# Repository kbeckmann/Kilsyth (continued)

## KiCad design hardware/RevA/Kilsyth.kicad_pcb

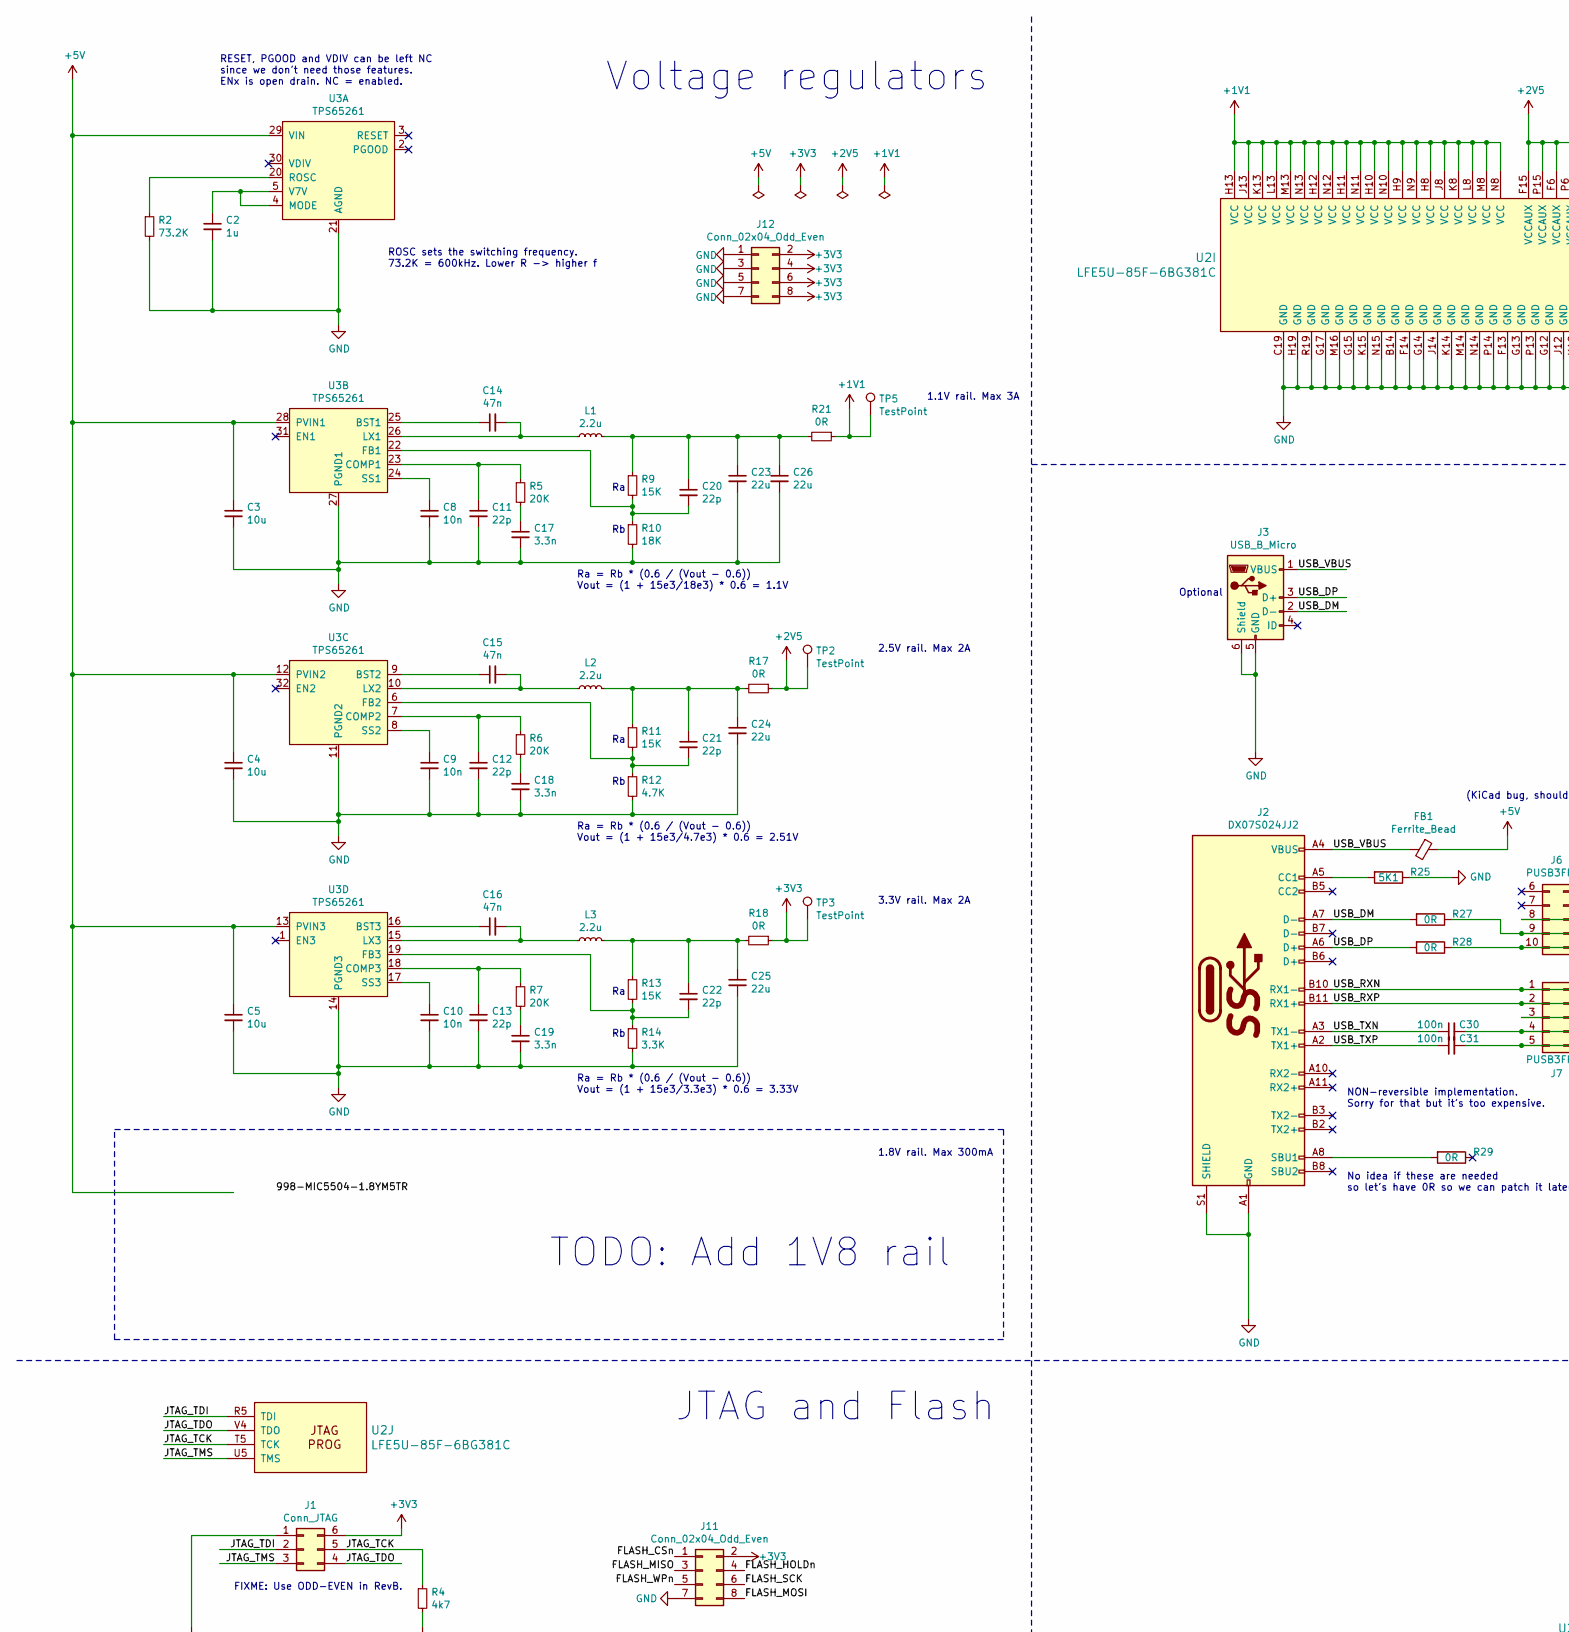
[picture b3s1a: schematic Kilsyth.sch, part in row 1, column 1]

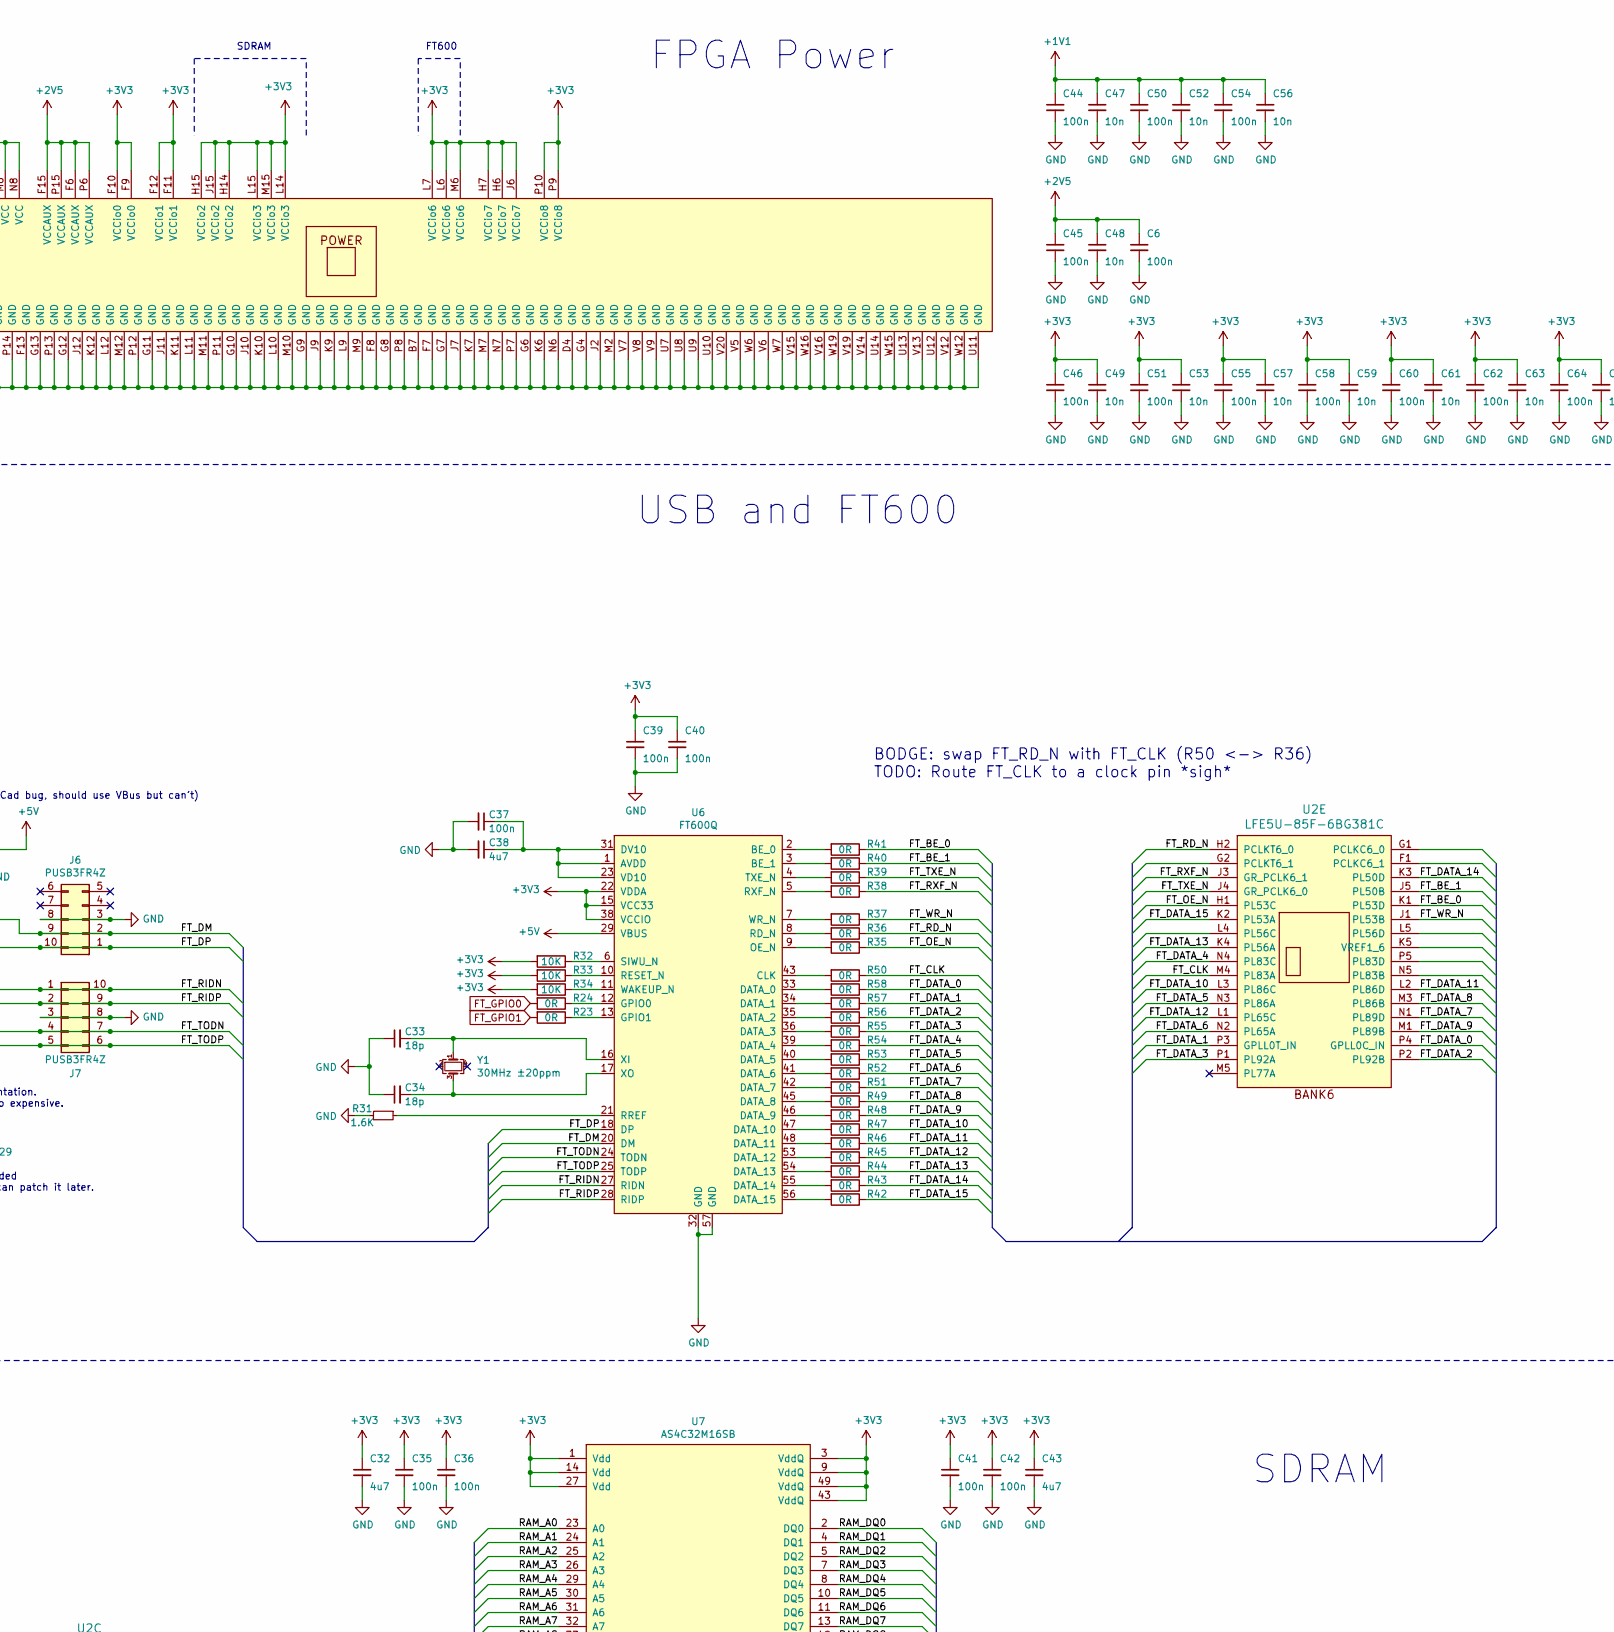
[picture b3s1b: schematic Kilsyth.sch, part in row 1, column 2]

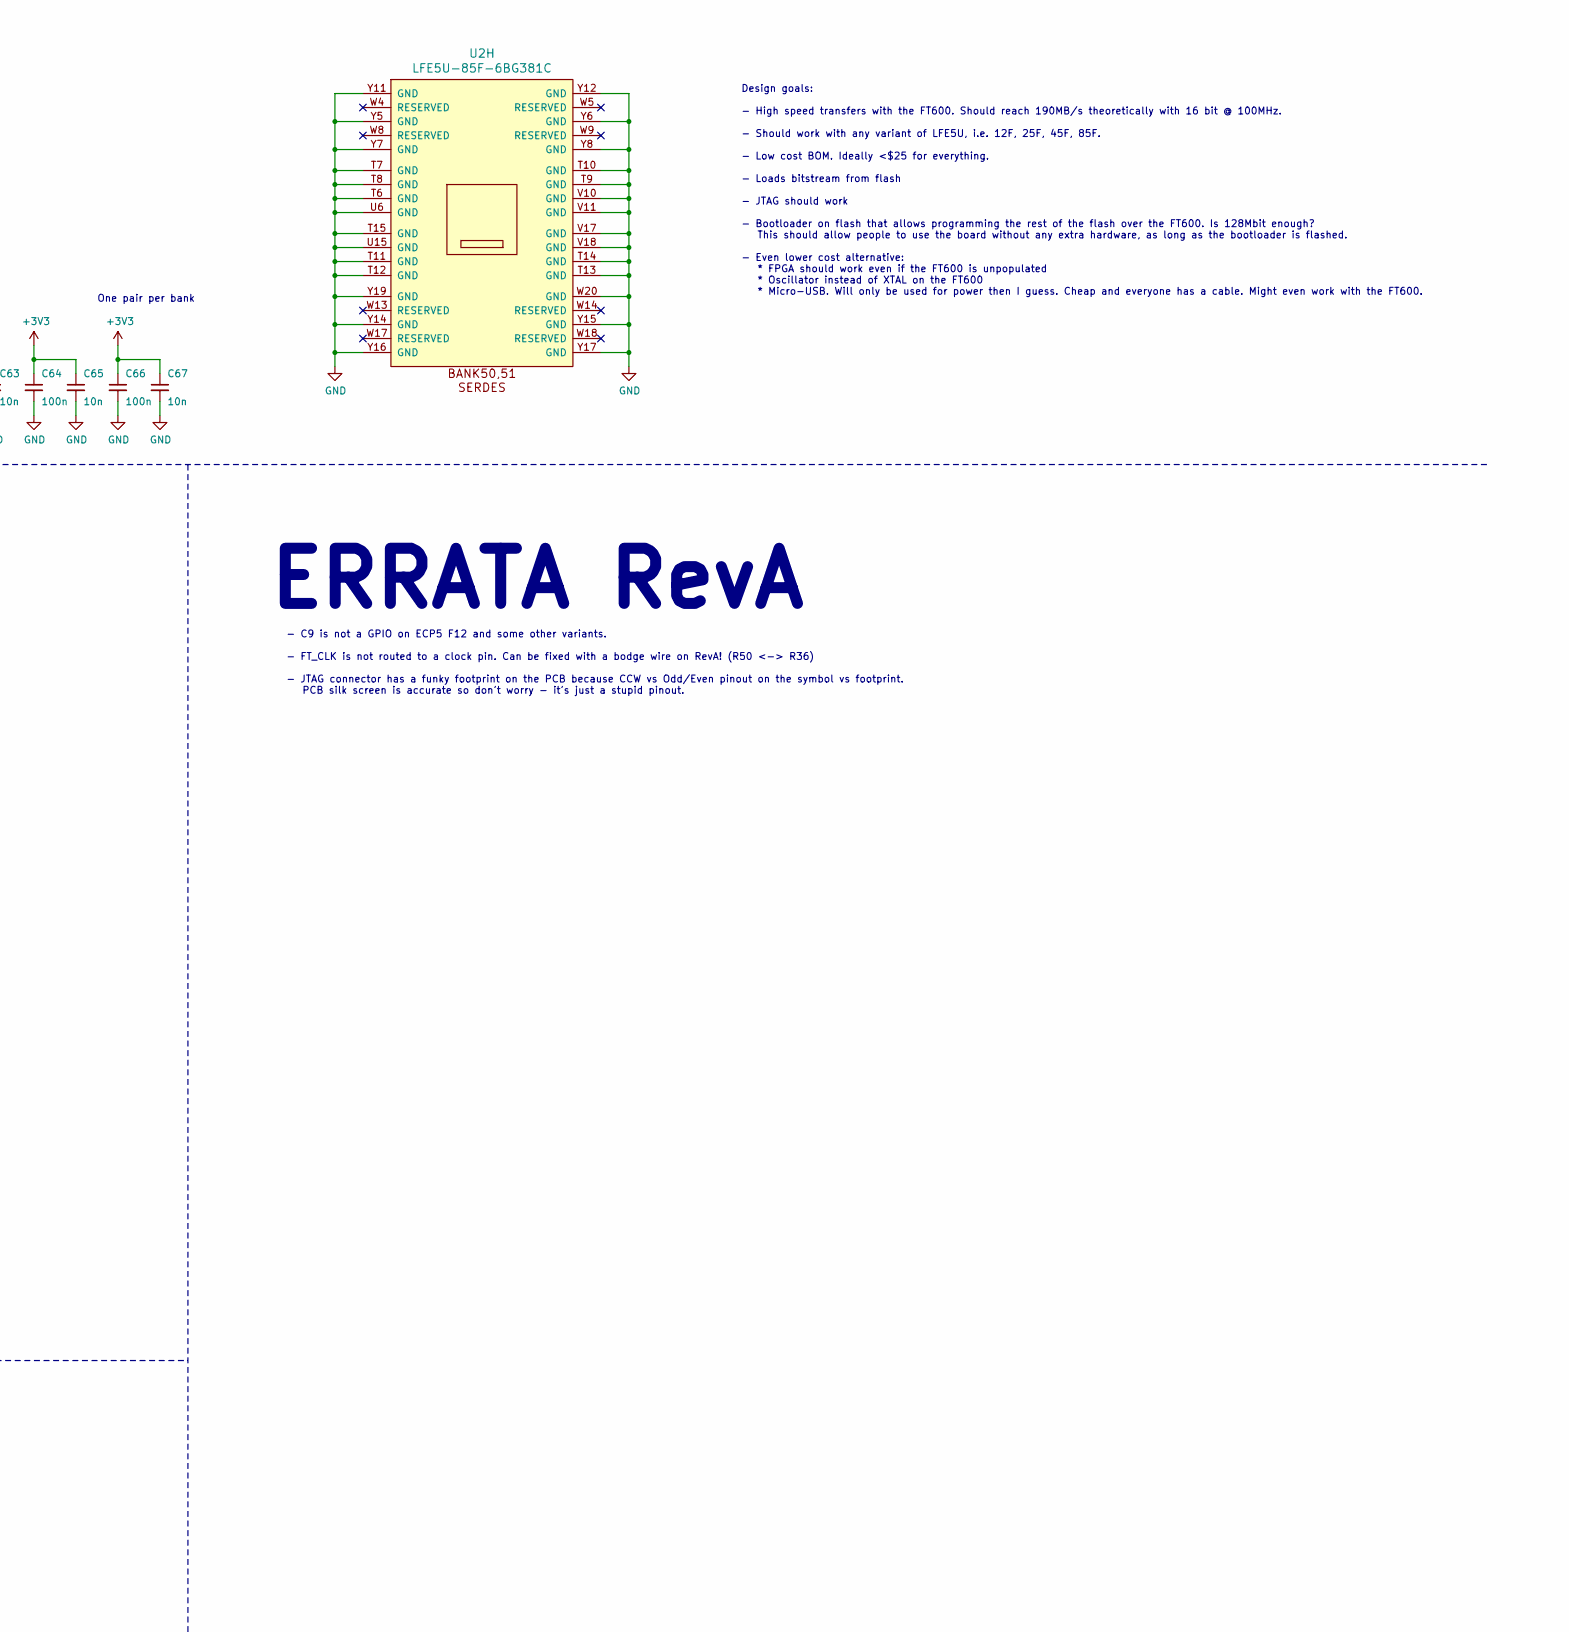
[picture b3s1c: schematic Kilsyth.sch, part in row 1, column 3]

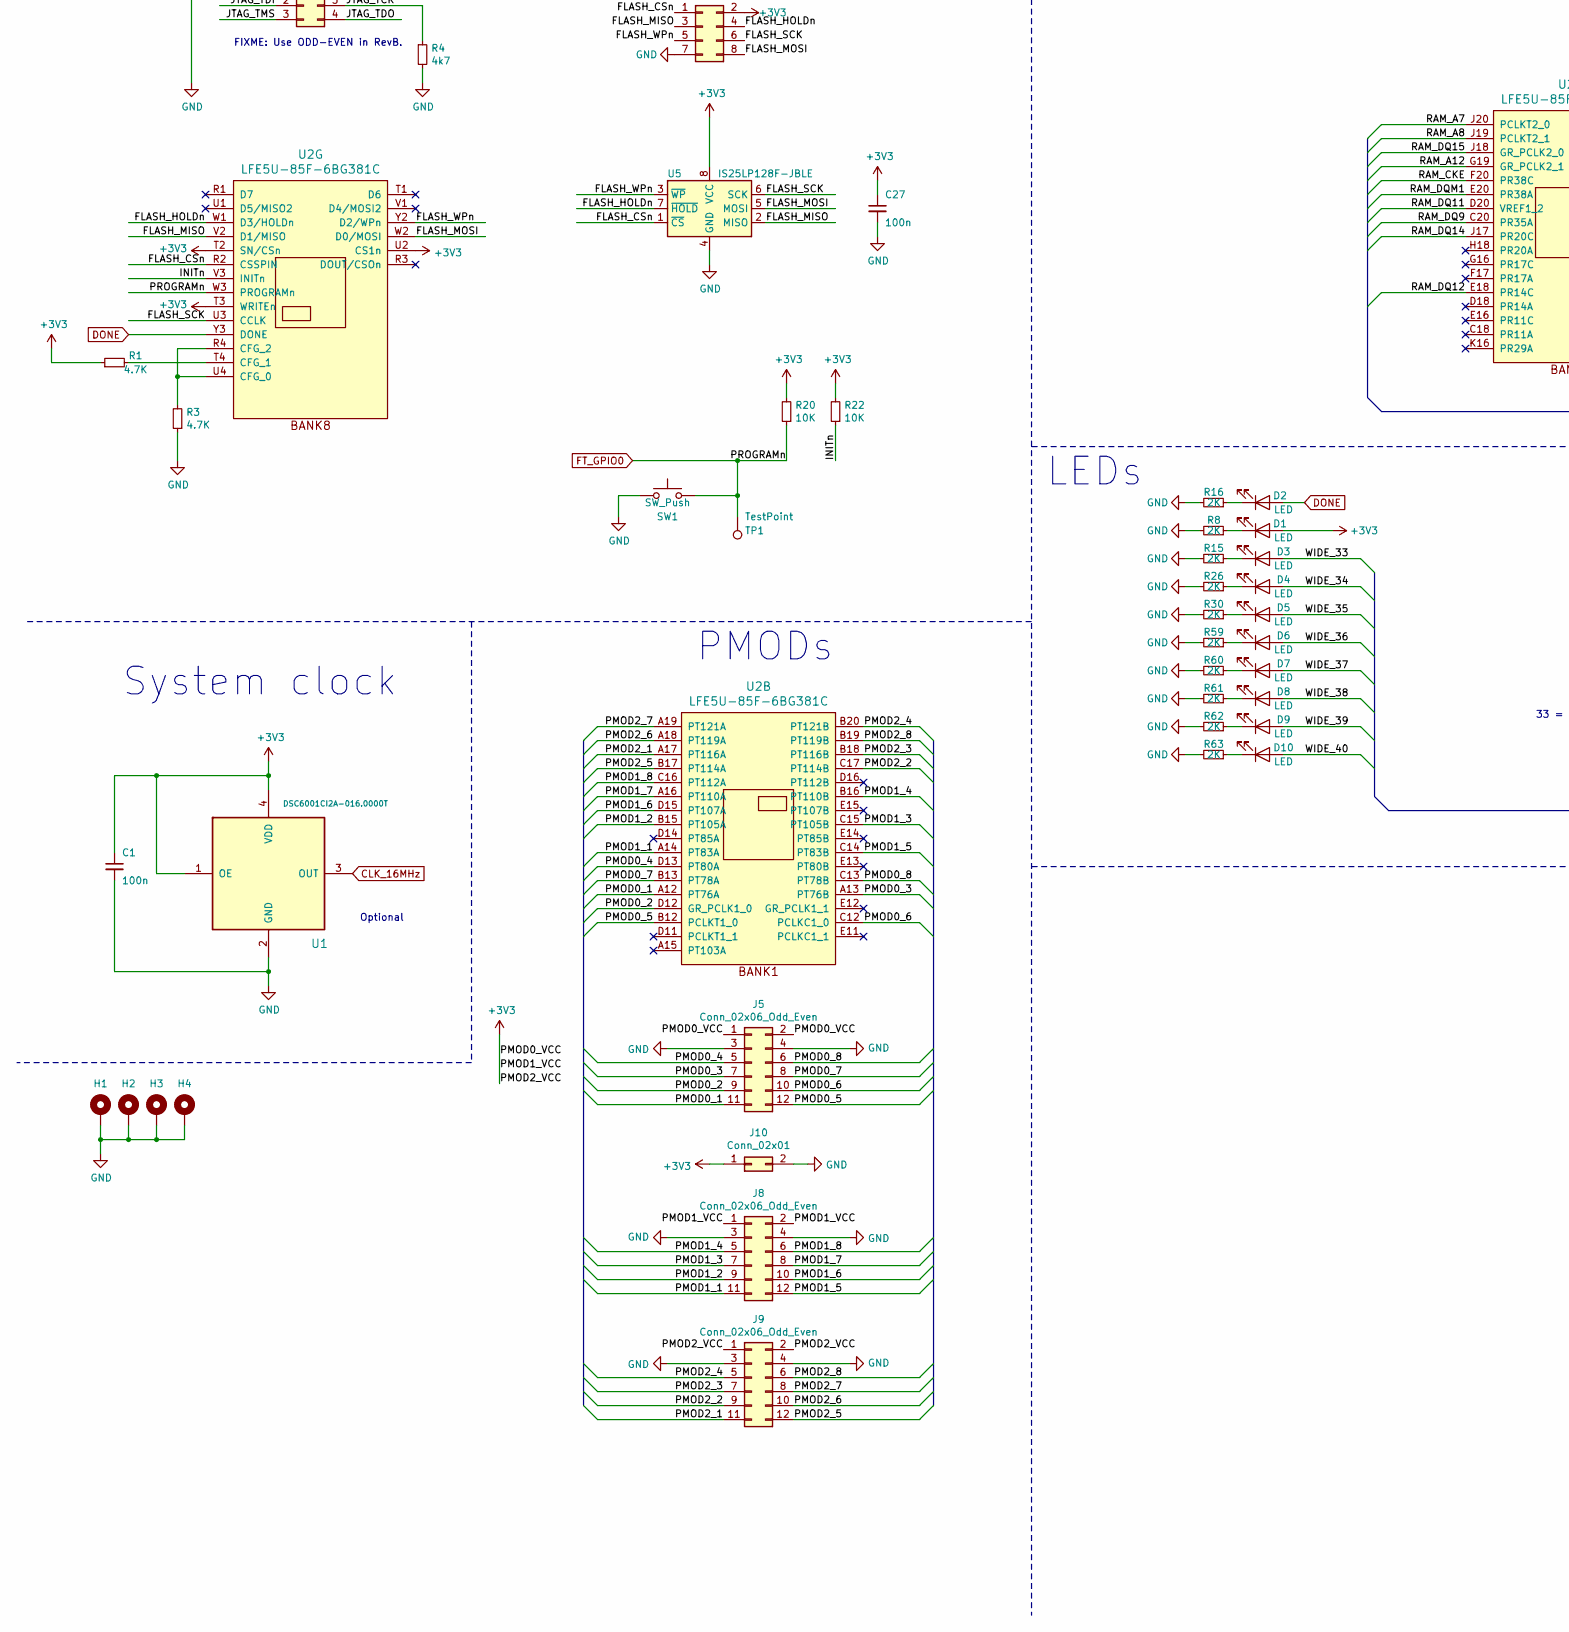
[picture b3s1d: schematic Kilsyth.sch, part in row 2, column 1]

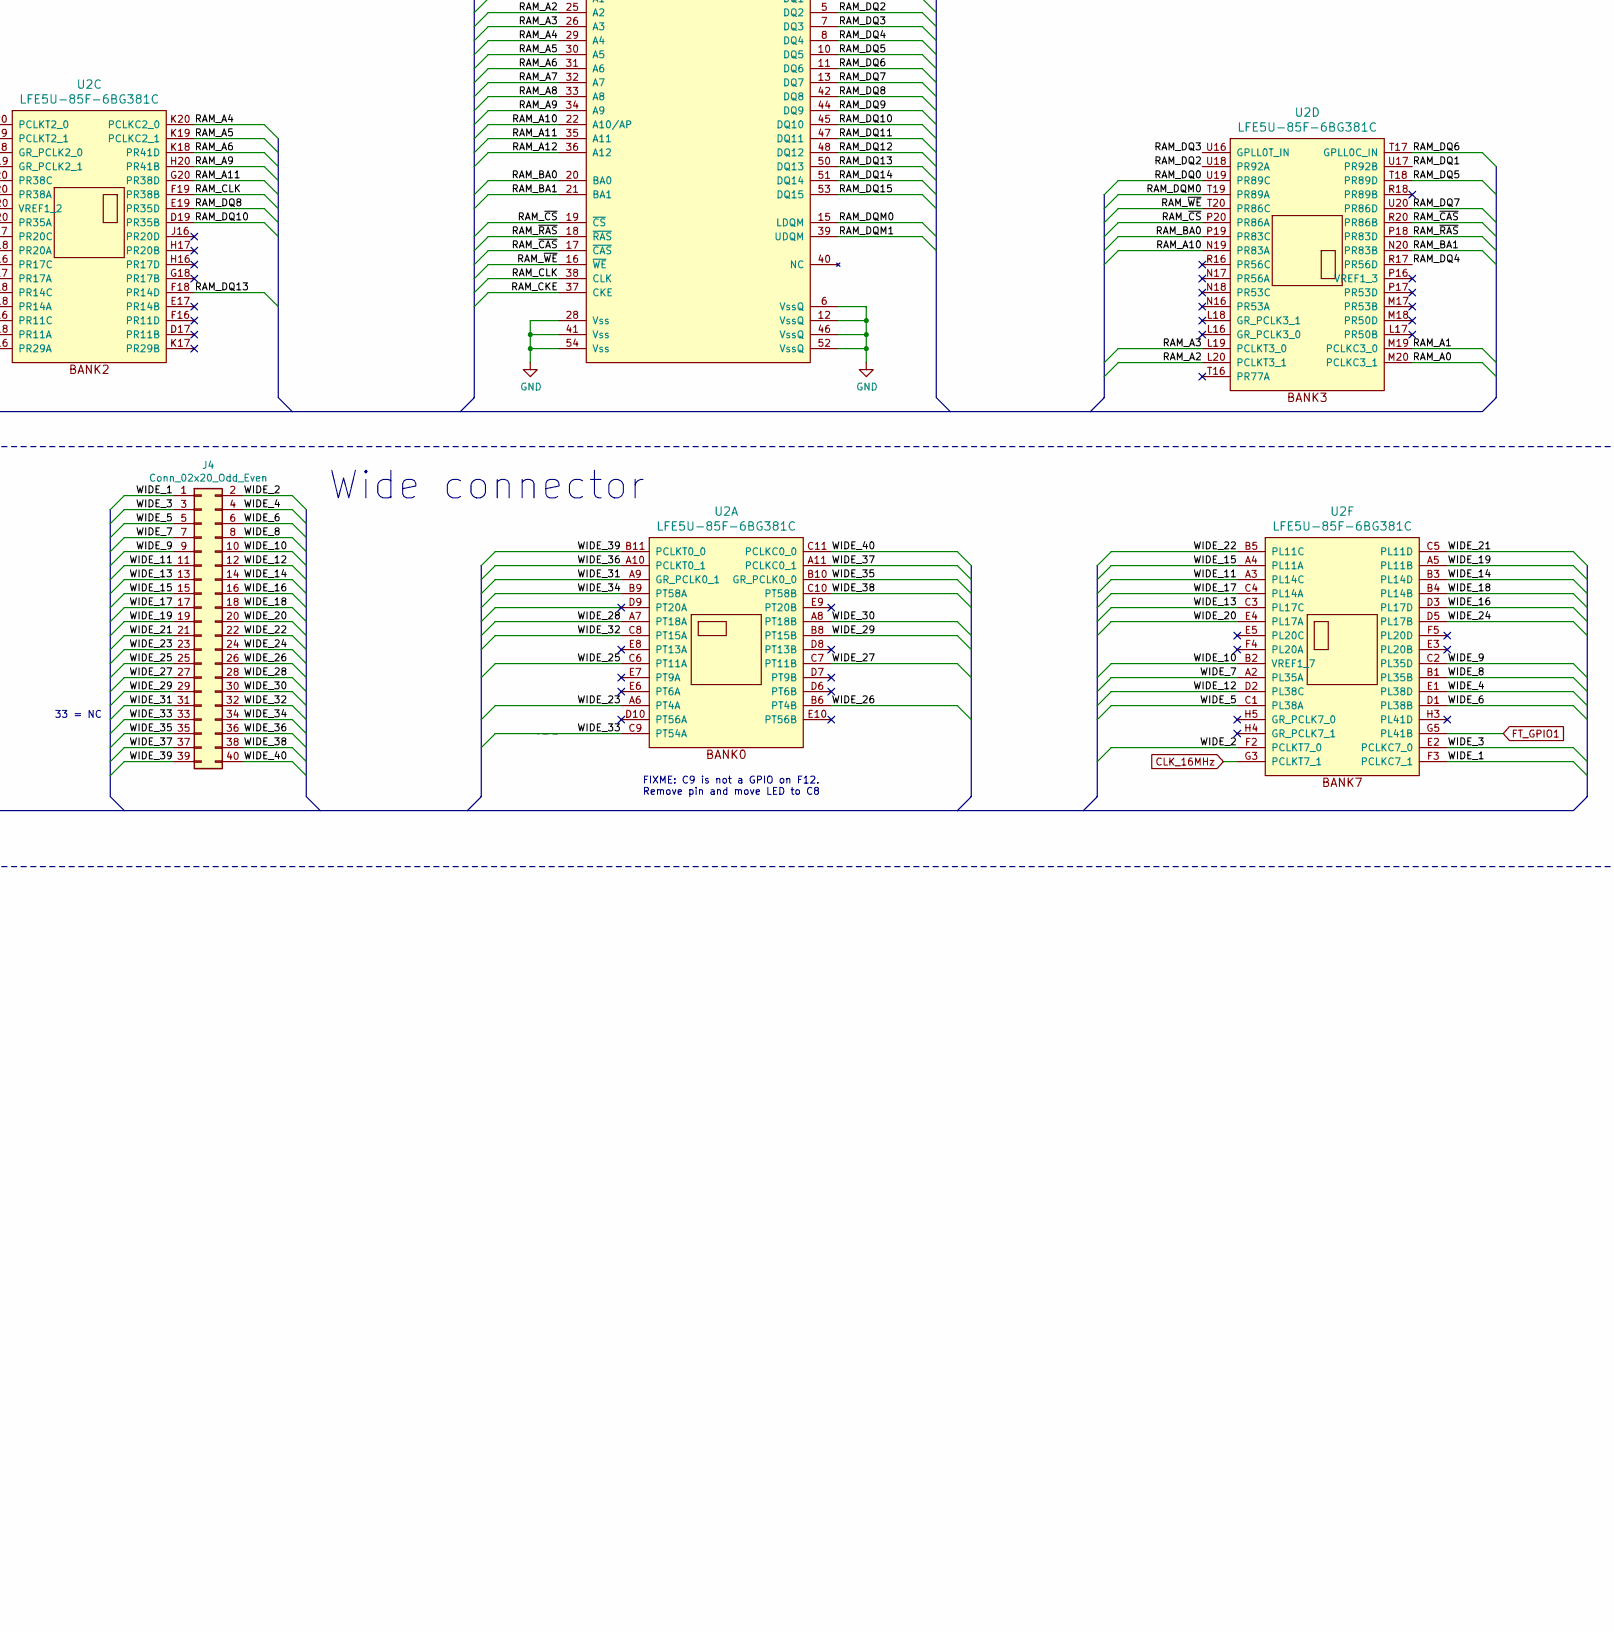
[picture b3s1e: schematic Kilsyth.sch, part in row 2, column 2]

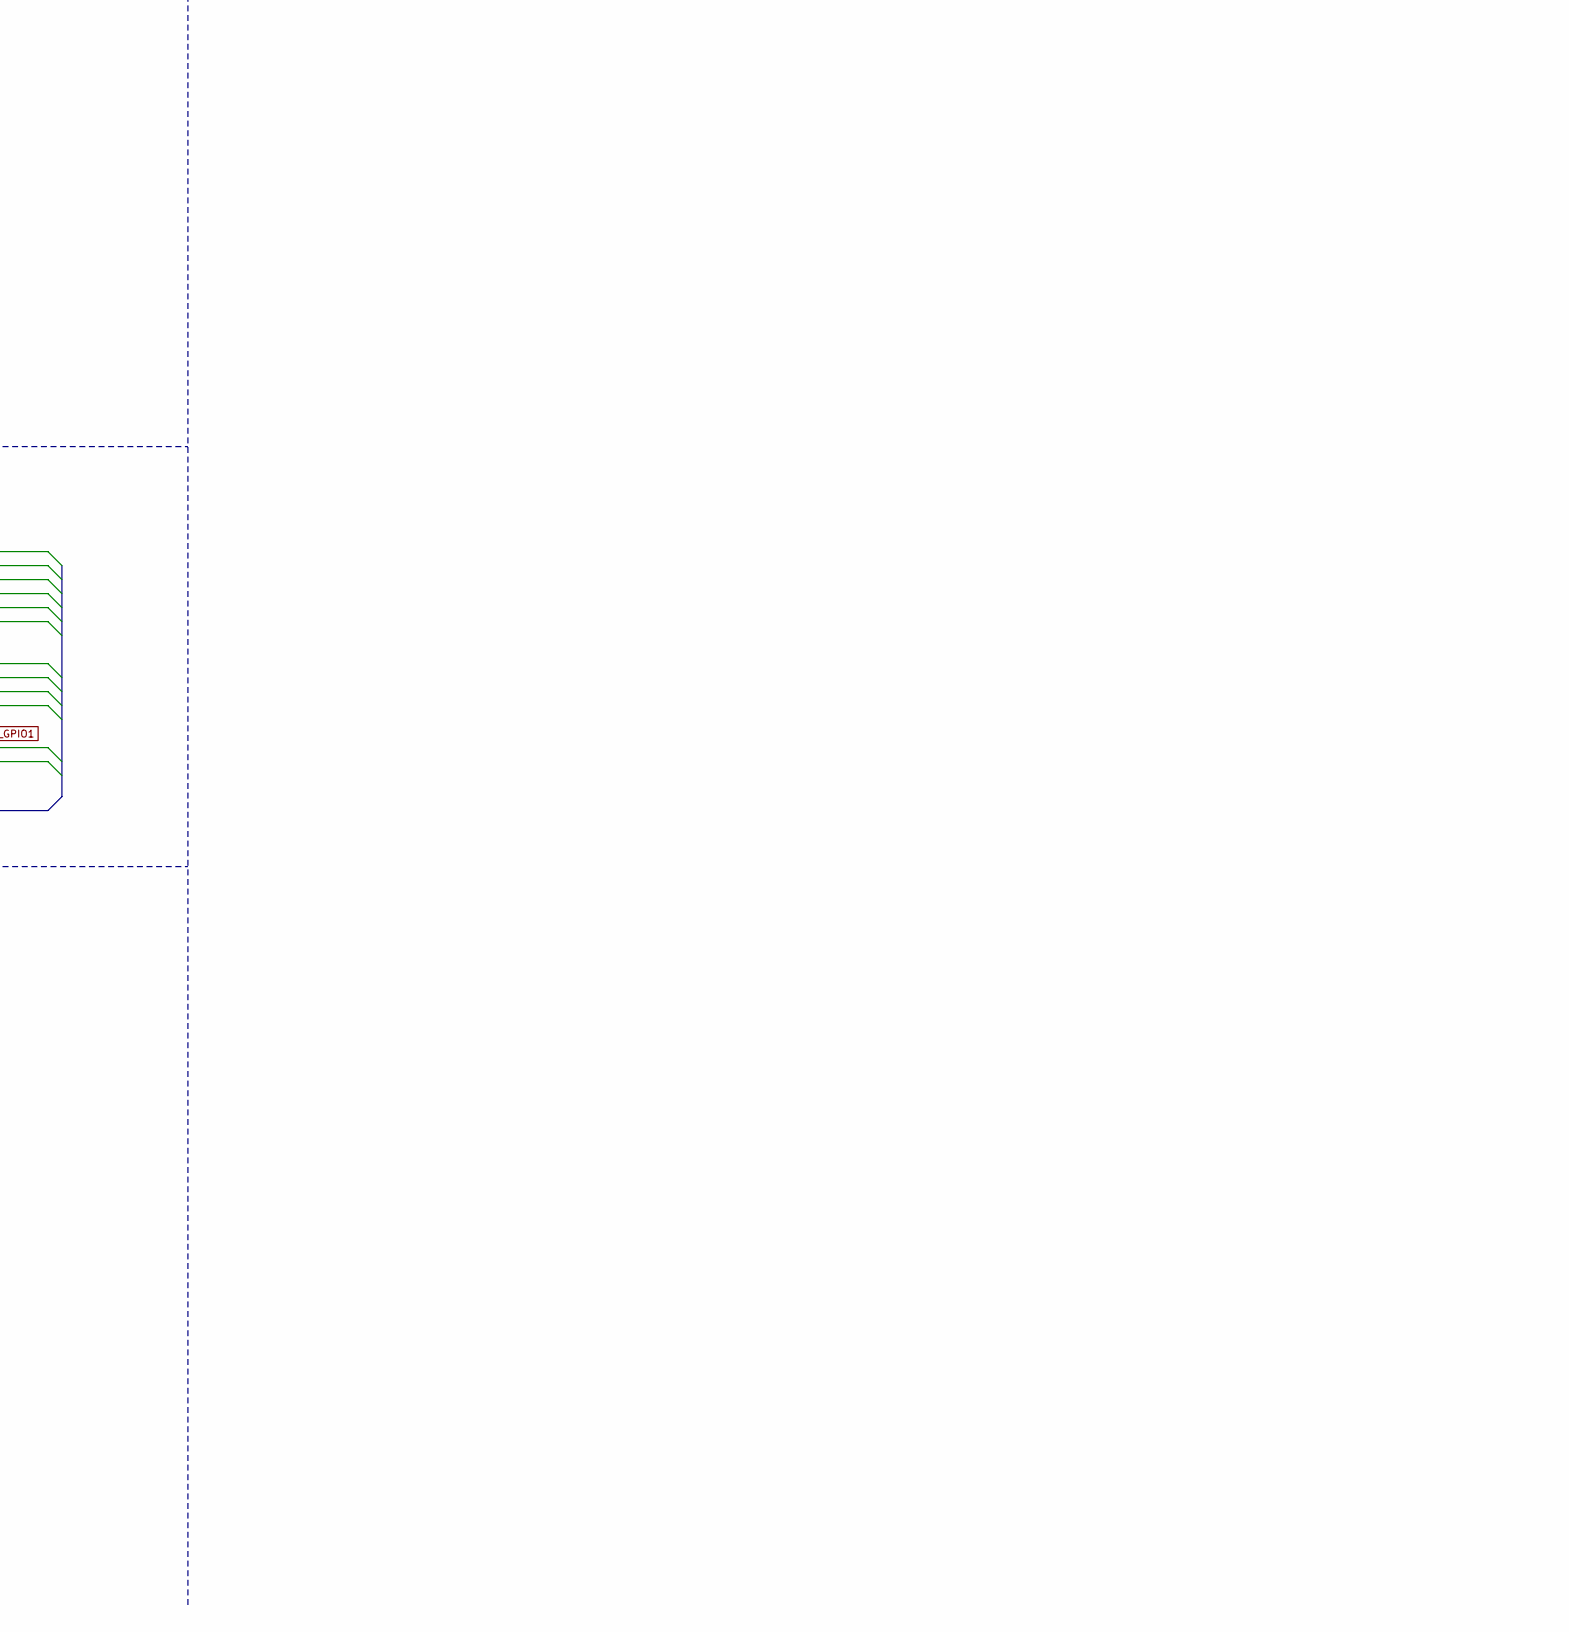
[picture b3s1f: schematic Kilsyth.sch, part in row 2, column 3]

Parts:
C1, C6, C27, C30, C31, C35, C36, C37, C39, C40, C41, C42, C44, C45, C46, C50, C51, C54, C55, C58, C60, C62, C64, C66: 100n; C_0603_1608Metric
C2: 1u; C_0603_1608Metric
C3, C4, C5: 10u; C_0603_1608Metric
C8, C9, C10, C47, C48, C49, C52, C53, C56, C57, C59, C61, C63, C65, C67: 10n; C_0603_1608Metric
C11, C12, C13, C20, C21, C22: 22p; C_0603_1608Metric
C14, C15, C16: 47n; C_0603_1608Metric
C17, C18, C19: 3.3n; C_0603_1608Metric
C23, C24, C25, C26: 22u; C_0603_1608Metric
C32, C38, C43: 4u7; C_0603_1608Metric
C33, C34: 18p; C_0603_1608Metric
D1, D2, D3, D4, D5, D6, D7, D8, D9, D10: LED; LED_0603_1608Metric
FB1: Ferrite_Bead; L_0603_1608Metric
H1, H2, H3, H4: MountingHole_3.2mm_M3_Pad
J1: Conn_JTAG; PinHeader_2x03_P2.54mm_Vertical_SMD
J2: DX07S024JJ2; USBC_DX07S024JJ2R1300; Mouser 656-DX07S024JJ2R1300
J3: USB_B_Micro; USB_Micro-B_Molex-105017-0001
J4: Conn_02x20_Odd_Even; PinHeader_2x20_P2.54mm_Vertical_SMD
J5, J8, J9: Conn_02x06_Odd_Even; PinSocket_2x06_P2.54mm_Horizontal
J6, J7: PUSB3FR4Z; Mouser 771-PUSB3FR4Z
J10: Conn_02x01; PinHeader_2x01_P2.54mm_Vertical
J11, J12: Conn_02x04_Odd_Even; PinHeader_2x04_P2.54mm_Vertical_SMD
L1, L2, L3: 2.2u; L_1008_1210; Mouser 81-DFE322512F-2R2MP2
R1, R3, R12: 4.7K; R_0603_1608Metric
R2: 73.2K; R_0603_1608Metric
R4: 4k7; R_0603_1608Metric
R5, R6, R7: 20K; R_0603_1608Metric
R8, R15, R16, R26, R30, R59, R60, R61, R62, R63: 2K; R_0603_1608Metric
R9, R11, R13: 15K; R_0603_1608Metric
R10: 18K; R_0603_1608Metric
R14: 3.3K; R_0603_1608Metric
R17, R18, R21, R23, R24, R27, R28, R29, R35, R36, R37, R38, R39, R40, R41, R42, R43, R44, R45, R46, R47, R48, R49, R50, R51, R52, R53, R54, R55, R56, R57, R58: 0R; R_0603_1608Metric
R20, R22, R32, R33, R34: 10K; R_0603_1608Metric
R25: 5K1; R_0603_1608Metric
R31: 1.6K; R_0603_1608Metric
SW1: SW_Push; SmallButton
TP1, TP2, TP3, TP5: TestPoint; TestPoint_Pad_D1.0mm
U1: DSC6001CI2A-016.0000T; Crystal_SMD_3225-4Pin_3.2x2.5mm; Mouser 579-6001CI2A0160000T
U2: LFE5U-85F-6BG381C; BGA-381_pitch0.8mm_dia0.4mm
U3: TPS65261; S-PVQFN-N32; Mouser 595-TPS65261RHBR
U5: IS25LP128F-JBLE; SOA008-150-208mil; Mouser 870-IS25LP128F-JBLE
U6: FT600Q; QFN-56-1EP_7x7mm_P0.4mm_EP5.7x5.7mm_FIXED; Mouser 895-FT600Q-B-T
U7: AS4C32M16SB; TSOP-II-54_22.2x10.16mm_P0.8mm
Y1: 30MHz ±20ppm; Crystal_SMD_2016-4Pin_2.0x1.6mm; Part number XRCPB30M000F2P00R0

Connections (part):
+1V1: C44.1, C47.1, C50.1, C52.1, C54.1, C56.1, R21.1, TP5.1, U2.H8 (VCC), U2.H9 (VCC), U2.H10 (VCC), U2.H11 (VCC), U2.H12 (VCC), U2.H13 (VCC), U2.J8 (VCC), U2.J13 (VCC), U2.K8 (VCC), U2.K13 (VCC), U2.L8 (VCC), U2.L13 (VCC), U2.M8 (VCC), U2.M13 (VCC), U2.N8 (VCC), U2.N9 (VCC), U2.N10 (VCC), U2.N11 (VCC), U2.N12 (VCC), U2.N13 (VCC)
+2V5: C6.1, C45.1, C48.1, R17.1, TP2.1, U2.F6 (VCCAUX), U2.F15 (VCCAUX), U2.P6 (VCCAUX), U2.P15 (VCCAUX)
+3V3: C1.1, C27.1, C32.1, C35.1, C36.1, C39.1, C40.1, C41.1, C42.1, C43.1, C46.1, C49.1, C51.1, C53.1, C55.1, C57.1, C58.1, C59.1, C60.1, C61.1, C62.1, C63.1, C64.1, C65.1, C66.1, C67.1, D1.2 (A), J1.6, J5.1, J5.2, J8.1, J8.2, J9.1, J9.2, J10.1, J11.2, J12.2, J12.4, J12.6, J12.8, R1.1, R18.1, R20.2, R22.2, R32.2, R33.2, R34.2, TP3.1, U1.1 (OE), U1.4 (VDD), U2.F9 (VCCio0), U2.F10 (VCCio0), U2.F11 (VCCio1), U2.F12 (VCCio1), U2.H6 (VCCio7), U2.H7 (VCCio7), U2.H14 (VCCio2), U2.H15 (VCCio2), U2.J6 (VCCio7), U2.J15 (VCCio2), U2.L6 (VCCio6), U2.L7 (VCCio6), U2.L14 (VCCio3), U2.L15 (VCCio3), U2.M6 (VCCio6), U2.M15 (VCCio3), U2.P9 (VCCio8), U2.P10 (VCCio8), U2.T2 (SN/CSn), U2.T3 (WRITEn), U2.U2 (CS1n), U5.8 (VCC), U6.15 (VCC33), U6.19 (VCC33), U6.22 (VDDA), U6.30 (VCC33), U6.38 (VCCIO), U6.44 (VCCIO), U6.52 (VCCIO), U7.1 (Vdd), U7.3 (VddQ)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
+5V: C3.1, C4.1, C5.1, FB1.1, U3.12 (PVIN2), U3.13 (PVIN3), U3.28 (PVIN1), U3.29 (VIN), U6.29 (VBUS)
/FLASH_CSn: J11.1, U2.R2 (CSSPIN), U5.1 (~CS)
/FLASH_HOLDn: J11.4, U2.W1 (D3/HOLDn), U5.7 (~HOLD)
/FLASH_MISO: J11.3, U2.V2 (D1/MISO), U5.2 (MISO)
/FLASH_MOSI: J11.8, U2.W2 (D0/MOSI), U5.5 (MOSI)
/FLASH_SCK: J11.6, U2.U3 (CCLK), U5.6 (SCK)
/FLASH_WPn: J11.5, U2.Y2 (D2/WPn), U5.3 (~WP)
/FT_BE_0: R41.1, U2.K1 (PL53D)
/FT_BE_1: R40.1, U2.J5 (PL50B)
/FT_CLK: R50.1, U2.M4 (PL83A)
/FT_DATA_0: R58.1, U2.P4 (GPLL0C_IN)
/FT_DATA_1: R57.1, U2.P3 (GPLL0T_IN)
/FT_DATA_2: R56.1, U2.P2 (PL92B)
/FT_DATA_3: R55.1, U2.P1 (PL92A)
/FT_DATA_4: R54.1, U2.N4 (PL83C)
/FT_DATA_5: R53.1, U2.N3 (PL86A)
/FT_DATA_6: R52.1, U2.N2 (PL65A)
/FT_DATA_7: R51.1, U2.N1 (PL89D)
/FT_DATA_8: R49.1, U2.M3 (PL86B)
/FT_DATA_9: R48.1, U2.M1 (PL89B)
/FT_DATA_10: R47.1, U2.L3 (PL86C)
/FT_DATA_11: R46.1, U2.L2 (PL86D)
/FT_DATA_12: R45.1, U2.L1 (PL65C)
/FT_DATA_13: R44.1, U2.K4 (PL56A)
/FT_DATA_14: R43.1, U2.K3 (PL50D)
/FT_DATA_15: R42.1, U2.K2 (PL53A)
/FT_DM: J6.2, J6.9, R27.1, U6.20 (DM)
/FT_DP: J6.1, J6.10, R28.1, U6.18 (DP)
/FT_OE_N: R35.1, U2.H1 (PL53C)
/FT_RD_N: R36.1, U2.H2 (PCLKT6_0)
/FT_RIDN: J2.B10 (RX1-), J7.1, J7.10, U6.27 (RIDN)
/FT_RIDP: J2.B11 (RX1+), J7.2, J7.9, U6.28 (RIDP)
/FT_RXF_N: R38.1, U2.J3 (GR_PCLK6_1)
/FT_TODN: C30.2, J7.4, J7.7, U6.24 (TODN)
/FT_TODP: C31.2, J7.5, J7.6, U6.25 (TODP)
/FT_TXE_N: R39.1, U2.J4 (GR_PCLK6_0)
/FT_WR_N: R37.1, U2.J1 (PL53B)
/INITn: R22.1, U2.V3 (INITn)
/JTAG_TCK: J1.5, R4.1, U2.T5 (TCK)
/JTAG_TDI: J1.2, U2.R5 (TDI)
/JTAG_TDO: J1.4, U2.V4 (TDO)
/JTAG_TMS: J1.3, U2.U5 (TMS)
/PMOD0_1: J5.11, U2.A12 (PT76A)
/PMOD0_2: J5.9, U2.D12 (GR_PCLK1_0)
/PMOD0_3: J5.7, U2.A13 (PT76B)
/PMOD0_4: J5.5, U2.D13 (PT80A)
/PMOD0_5: J5.12, U2.B12 (PCLKT1_0)
/PMOD0_6: J5.10, U2.C12 (PCLKC1_0)
/PMOD0_7: J5.8, U2.B13 (PT78A)
/PMOD0_8: J5.6, U2.C13 (PT78B)
/PMOD1_1: J8.11, U2.A14 (PT83A)
/PMOD1_2: J8.9, U2.B15 (PT105A)
/PMOD1_3: J8.7, U2.C15 (PT105B)
/PMOD1_4: J8.5, U2.B16 (PT110B)
/PMOD1_5: J8.12, U2.C14 (PT83B)
/PMOD1_6: J8.10, U2.D15 (PT107A)
/PMOD1_7: J8.8, U2.A16 (PT110A)
/PMOD1_8: J8.6, U2.C16 (PT112A)
/PMOD2_1: J9.11, U2.A17 (PT116A)
/PMOD2_2: J9.9, U2.C17 (PT114B)
/PMOD2_3: J9.7, U2.B18 (PT116B)
/PMOD2_4: J9.5, U2.B20 (PT121B)
/PMOD2_5: J9.12, U2.B17 (PT114A)
/PMOD2_6: J9.10, U2.A18 (PT119A)
/PMOD2_7: J9.8, U2.A19 (PT121A)
/PMOD2_8: J9.6, U2.B19 (PT119B)
/RAM_A0: U2.M20 (PCLKC3_1), U7.23 (A0)
/RAM_A1: U2.M19 (PCLKC3_0), U7.24 (A1)
/RAM_A2: U2.L20 (PCLKT3_1), U7.25 (A2)
/RAM_A3: U2.L19 (PCLKT3_0), U7.26 (A3)
/RAM_A4: U2.K20 (PCLKC2_0), U7.29 (A4)
/RAM_A5: U2.K19 (PCLKC2_1), U7.30 (A5)
/RAM_A6: U2.K18 (PR41D), U7.31 (A6)
/RAM_A7: U2.J20 (PCLKT2_0), U7.32 (A7)
/RAM_A8: U2.J19 (PCLKT2_1), U7.33 (A8)
/RAM_A9: U2.H20 (PR41B), U7.34 (A9)
/RAM_A10: U2.N19 (PR83A), U7.22 (A10/AP)
/RAM_A11: U2.G20 (PR38D), U7.35 (A11)
/RAM_A12: U2.G19 (GR_PCLK2_1), U7.36 (A12)
/RAM_BA0: U2.P19 (PR83C), U7.20 (BA0)
/RAM_BA1: U2.N20 (PR83B), U7.21 (BA1)
/RAM_CKE: U2.F20 (PR38C), U7.37 (CKE)
/RAM_CLK: U2.F19 (PR38B), U7.38 (CLK)
/RAM_DQ0: U2.U19 (PR89C), U7.2 (DQ0)
/RAM_DQ1: U2.U17 (PR92B), U7.4 (DQ1)
/RAM_DQ2: U2.U18 (PR92A), U7.5 (DQ2)
/RAM_DQ3: U2.U16 (GPLL0T_IN), U7.7 (DQ3)
/RAM_DQ4: U2.R17 (PR56D), U7.8 (DQ4)
/RAM_DQ5: U2.T18 (PR89D), U7.10 (DQ5)
/RAM_DQ6: U2.T17 (GPLL0C_IN), U7.11 (DQ6)
/RAM_DQ7: U2.U20 (PR86D), U7.13 (DQ7)
/RAM_DQ8: U2.E19 (PR35D), U7.42 (DQ8)
/RAM_DQ9: U2.C20 (PR35A), U7.44 (DQ9)
/RAM_DQ10: U2.D19 (PR35B), U7.45 (DQ10)
/RAM_DQ11: U2.D20 (VREF1_2), U7.47 (DQ11)
/RAM_DQ12: U2.E18 (PR14C), U7.48 (DQ12)
/RAM_DQ13: U2.F18 (PR14D), U7.50 (DQ13)
/RAM_DQ14: U2.J17 (PR20C), U7.51 (DQ14)
/RAM_DQ15: U2.J18 (GR_PCLK2_0), U7.53 (DQ15)
/RAM_DQM0: U2.T19 (PR89A), U7.15 (LDQM)
/RAM_DQM1: U2.E20 (PR38A), U7.39 (UDQM)
/RAM_~CAS: U2.R20 (PR86B), U7.17 (~CAS)
/RAM_~CS: U2.P20 (PR86A), U7.19 (~CS)
/RAM_~RAS: U2.P18 (PR83D), U7.18 (~RAS)
/RAM_~WE: U2.T20 (PR86C), U7.16 (~WE)
/USB_DM: J2.A7 (D-), J3.2 (D-), R27.2
/USB_DP: J2.A6 (D+), J3.3 (D+), R28.2
/USB_TXN: C30.1, J2.A3 (TX1-)
/USB_TXP: C31.1, J2.A2 (TX1+)
/WIDE_1: J4.1, U2.F3 (PCLKC7_1)
/WIDE_2: J4.2, U2.F2 (PCLKT7_0)
/WIDE_3: J4.3, U2.E2 (PCLKC7_0)
/WIDE_4: J4.4, U2.E1 (PL38D)
/WIDE_5: J4.5, U2.C1 (PL38A)
/WIDE_6: J4.6, U2.D1 (PL38B)
/WIDE_7: J4.7, U2.A2 (PL35A)
/WIDE_8: J4.8, U2.B1 (PL35B)
/WIDE_9: J4.9, U2.C2 (PL35D)
/WIDE_10: J4.10, U2.B2 (VREF1_7)
/WIDE_11: J4.11, U2.A3 (PL14C)
/WIDE_12: J4.12, U2.D2 (PL38C)
/WIDE_13: J4.13, U2.C3 (PL17C)
/WIDE_14: J4.14, U2.B3 (PL14D)
/WIDE_15: J4.15, U2.A4 (PL11A)
/WIDE_16: J4.16, U2.D3 (PL17D)
/WIDE_17: J4.17, U2.C4 (PL14A)
/WIDE_18: J4.18, U2.B4 (PL14B)
/WIDE_19: J4.19, U2.A5 (PL11B)
/WIDE_20: J4.20, U2.E4 (PL17A)
/WIDE_21: J4.21, U2.C5 (PL11D)
/WIDE_22: J4.22, U2.B5 (PL11C)
/WIDE_23: J4.23, U2.A6 (PT4A)
/WIDE_24: J4.24, U2.D5 (PL17B)
/WIDE_25: J4.25, U2.C6 (PT11A)
/WIDE_26: J4.26, U2.B6 (PT4B)
/WIDE_27: J4.27, U2.C7 (PT11B)
/WIDE_28: J4.28, U2.A7 (PT18A)
/WIDE_29: J4.29, U2.B8 (PT15B)
/WIDE_30: J4.30, U2.A8 (PT18B)
/WIDE_31: J4.31, U2.A9 (GR_PCLK0_1)
/WIDE_32: J4.32, U2.C8 (PT15A)
/WIDE_33: D3.2 (A), J4.33, U2.C9 (PT54A)
/WIDE_34: D4.2 (A), J4.34, U2.B9 (PT58A)
/WIDE_35: D5.2 (A), J4.35, U2.B10 (GR_PCLK0_0)
/WIDE_36: D6.2 (A), J4.36, U2.A10 (PCLKT0_1)
/WIDE_37: D7.2 (A), J4.37, U2.A11 (PCLKC0_1)
/WIDE_38: D8.2 (A), J4.38, U2.C10 (PT58B)
/WIDE_39: D9.2 (A), J4.39, U2.B11 (PCLKT0_0)
/WIDE_40: D10.2 (A), J4.40, U2.C11 (PCLKC0_0)
CLK_16MHz: U1.3 (OUT), U2.G3 (PCLKT7_1)
DONE: D2.2 (A), U2.Y3 (DONE)
FT_GPIO0: R20.1, R24.2, SW1.2, TP1.1, U2.W3 (PROGRAMn)
FT_GPIO1: R23.2, U2.G5 (PL41B)
GND: C1.2, C2.2, C3.2, C4.2, C5.2, C6.2, C8.2, C9.2, C10.2, C11.2, C12.2, C13.2, C17.2, C18.2, C19.2, C23.2, C24.2, C25.2, C26.2, C27.2, C32.2, C33.1, C34.1, C35.2, C36.2, C37.2, C38.2, C39.2, C40.2, C41.2, C42.2, C43.2, C44.2, C45.2, C46.2, C47.2, C48.2, C49.2, C50.2, C51.2, C52.2, C53.2, C54.2, C55.2, C56.2, C57.2, C58.2, C59.2, C60.2, C61.2, C62.2, C63.2, C64.2, C65.2, C66.2, C67.2, H1.1, H2.1, H3.1, H4.1, J1.1, J2.A1 (GND), J2.A12 (GND), J2.B1 (GND), J2.B12 (GND), J2.S1 (SHIELD), J3.5 (GND), J3.6 (Shield), J5.3, J5.4, J6.3, J6.8, J7.3, J7.8, J8.3, J8.4, J9.3, J9.4, J10.2, J11.7, J12.1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
unnamed: C2.1, U3.4 (MODE), U3.5 (V7V)
unnamed: C8.1, U3.24 (SS1)
unnamed: C9.1, U3.8 (SS2)
unnamed: C10.1, U3.17 (SS3)
unnamed: C11.1, R5.1, U3.23 (COMP1)
unnamed: C12.1, R6.1, U3.7 (COMP2)
unnamed: C13.1, R7.1, U3.18 (COMP3)
unnamed: C14.1, U3.25 (BST1)
unnamed: C14.2, L1.1, U3.26 (LX1)
unnamed: C15.1, U3.9 (BST2)
unnamed: C15.2, L2.1, U3.10 (LX2)
unnamed: C16.1, U3.16 (BST3)
unnamed: C16.2, L3.1, U3.15 (LX3)
unnamed: C17.1, R5.2
unnamed: C18.1, R6.2
unnamed: C19.1, R7.2
unnamed: C20.1, C23.1, C26.1, L1.2, R9.1, R21.2
unnamed: C20.2, R9.2, R10.1, U3.22 (FB1)
unnamed: C21.1, C24.1, L2.2, R11.1, R17.2
unnamed: C21.2, R11.2, R12.1, U3.6 (FB2)
unnamed: C22.1, C25.1, L3.2, R13.1, R18.2
unnamed: C22.2, R13.2, R14.1, U3.19 (FB3)
unnamed: C33.2, U6.16 (XI), Y1.1
unnamed: C34.2, U6.17 (XO), Y1.3
unnamed: D1.1 (K), R8.1
unnamed: D2.1 (K), R16.1
unnamed: D3.1 (K), R15.1
unnamed: D4.1 (K), R26.1
unnamed: D5.1 (K), R30.1
unnamed: D6.1 (K), R59.1
unnamed: D7.1 (K), R60.1
unnamed: D8.1 (K), R61.1
unnamed: D9.1 (K), R62.1
unnamed: D10.1 (K), R63.1
unnamed: J2.A5 (CC1), R25.2
unnamed: J2.A8 (SBU1), R29.2
unnamed: R1.2, U2.T4 (CFG_1)
unnamed: R2.1, U3.20 (ROSC)
unnamed: R3.2, U2.R4 (CFG_2), U2.U4 (CFG_0)
unnamed: R23.1, U6.13 (GPIO1)
unnamed: R24.1, U6.12 (GPIO0)
unnamed: R31.1, U6.21 (RREF)
unnamed: R32.1, U6.6 (SIWU_N)
unnamed: R33.1, U6.10 (RESET_N)
unnamed: R34.1, U6.11 (WAKEUP_N)
unnamed: R35.2, U6.9 (OE_N)
unnamed: R36.2, U6.8 (RD_N)
unnamed: R37.2, U6.7 (WR_N)
unnamed: R38.2, U6.5 (RXF_N)
unnamed: R39.2, U6.4 (TXE_N)
unnamed: R40.2, U6.3 (BE_1)
unnamed: R41.2, U6.2 (BE_0)
unnamed: R42.2, U6.56 (DATA_15)
unnamed: R43.2, U6.55 (DATA_14)
unnamed: R44.2, U6.54 (DATA_13)
unnamed: R45.2, U6.53 (DATA_12)
unnamed: R46.2, U6.48 (DATA_11)
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
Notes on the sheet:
Ra = Rb * (0.6 / (Vout - 0.6)) Vout = (1 + 15e3/18e3) * 0.6 = 1.1V
Ra = Rb * (0.6 / (Vout - 0.6)) Vout = (1 + 15e3/4.7e3) * 0.6 = 2.51V
Ra = Rb * (0.6 / (Vout - 0.6)) Vout = (1 + 15e3/3.3e3) * 0.6 = 3.33V
RESET, PGOOD and VDIV can be left NC since we don't need those features. ENx is open drain. NC = enabled.
3.3V rail. Max 2A
1.8V rail. Max 300mA
2.5V rail. Max 2A
1.1V rail. Max 3A
No idea if these are needed so let's have 0R so we can patch it later.
Design goals: - High speed transfers with the FT600. Should reach 190MB/s theoretically with 16 bit @ 100MHz. - Should work with any variant of LFE5U, i.e. 12F, 25F, 45F, 85F. - Low cost BOM. Ideally <$25 for everything. - Loads bitstream from flash - JTAG should work - Bootloader on flash that all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
Voltage regulators
USB and FT600
JTAG and Flash
FPGA Power
System clock
LEDs
Optional
SDRAM
FT600
ROSC sets the switching frequency. 73.2K = 600kHz. Lower R -> higher f
One pair per bank
(KiCad bug, should use VBus but can't)
NON-reversible implementation. Sorry for that but it's too expensive.
TODO: Add 1V8 rail
ERRATA RevA
- C9 is not a GPIO on ECP5 F12 and some other variants. - FT_CLK is not routed to a clock pin. Can be fixed with a bodge wire on RevA! (R50 <-> R36) - JTAG connector has a funky footprint on the PCB because CCW vs Odd/Even pinout on the symbol vs footprint. PCB silk screen is accurate so don't worr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
FIXME: C9 is not a GPIO on F12. Remove pin and move LED to C8
33 = NC
BODGE: swap FT_RD_N with FT_CLK (R50 <-> R36) TODO: Route FT_CLK to a clock pin *sigh*
PMODs
Wide connector
FIXME: Use ODD-EVEN in RevB.
